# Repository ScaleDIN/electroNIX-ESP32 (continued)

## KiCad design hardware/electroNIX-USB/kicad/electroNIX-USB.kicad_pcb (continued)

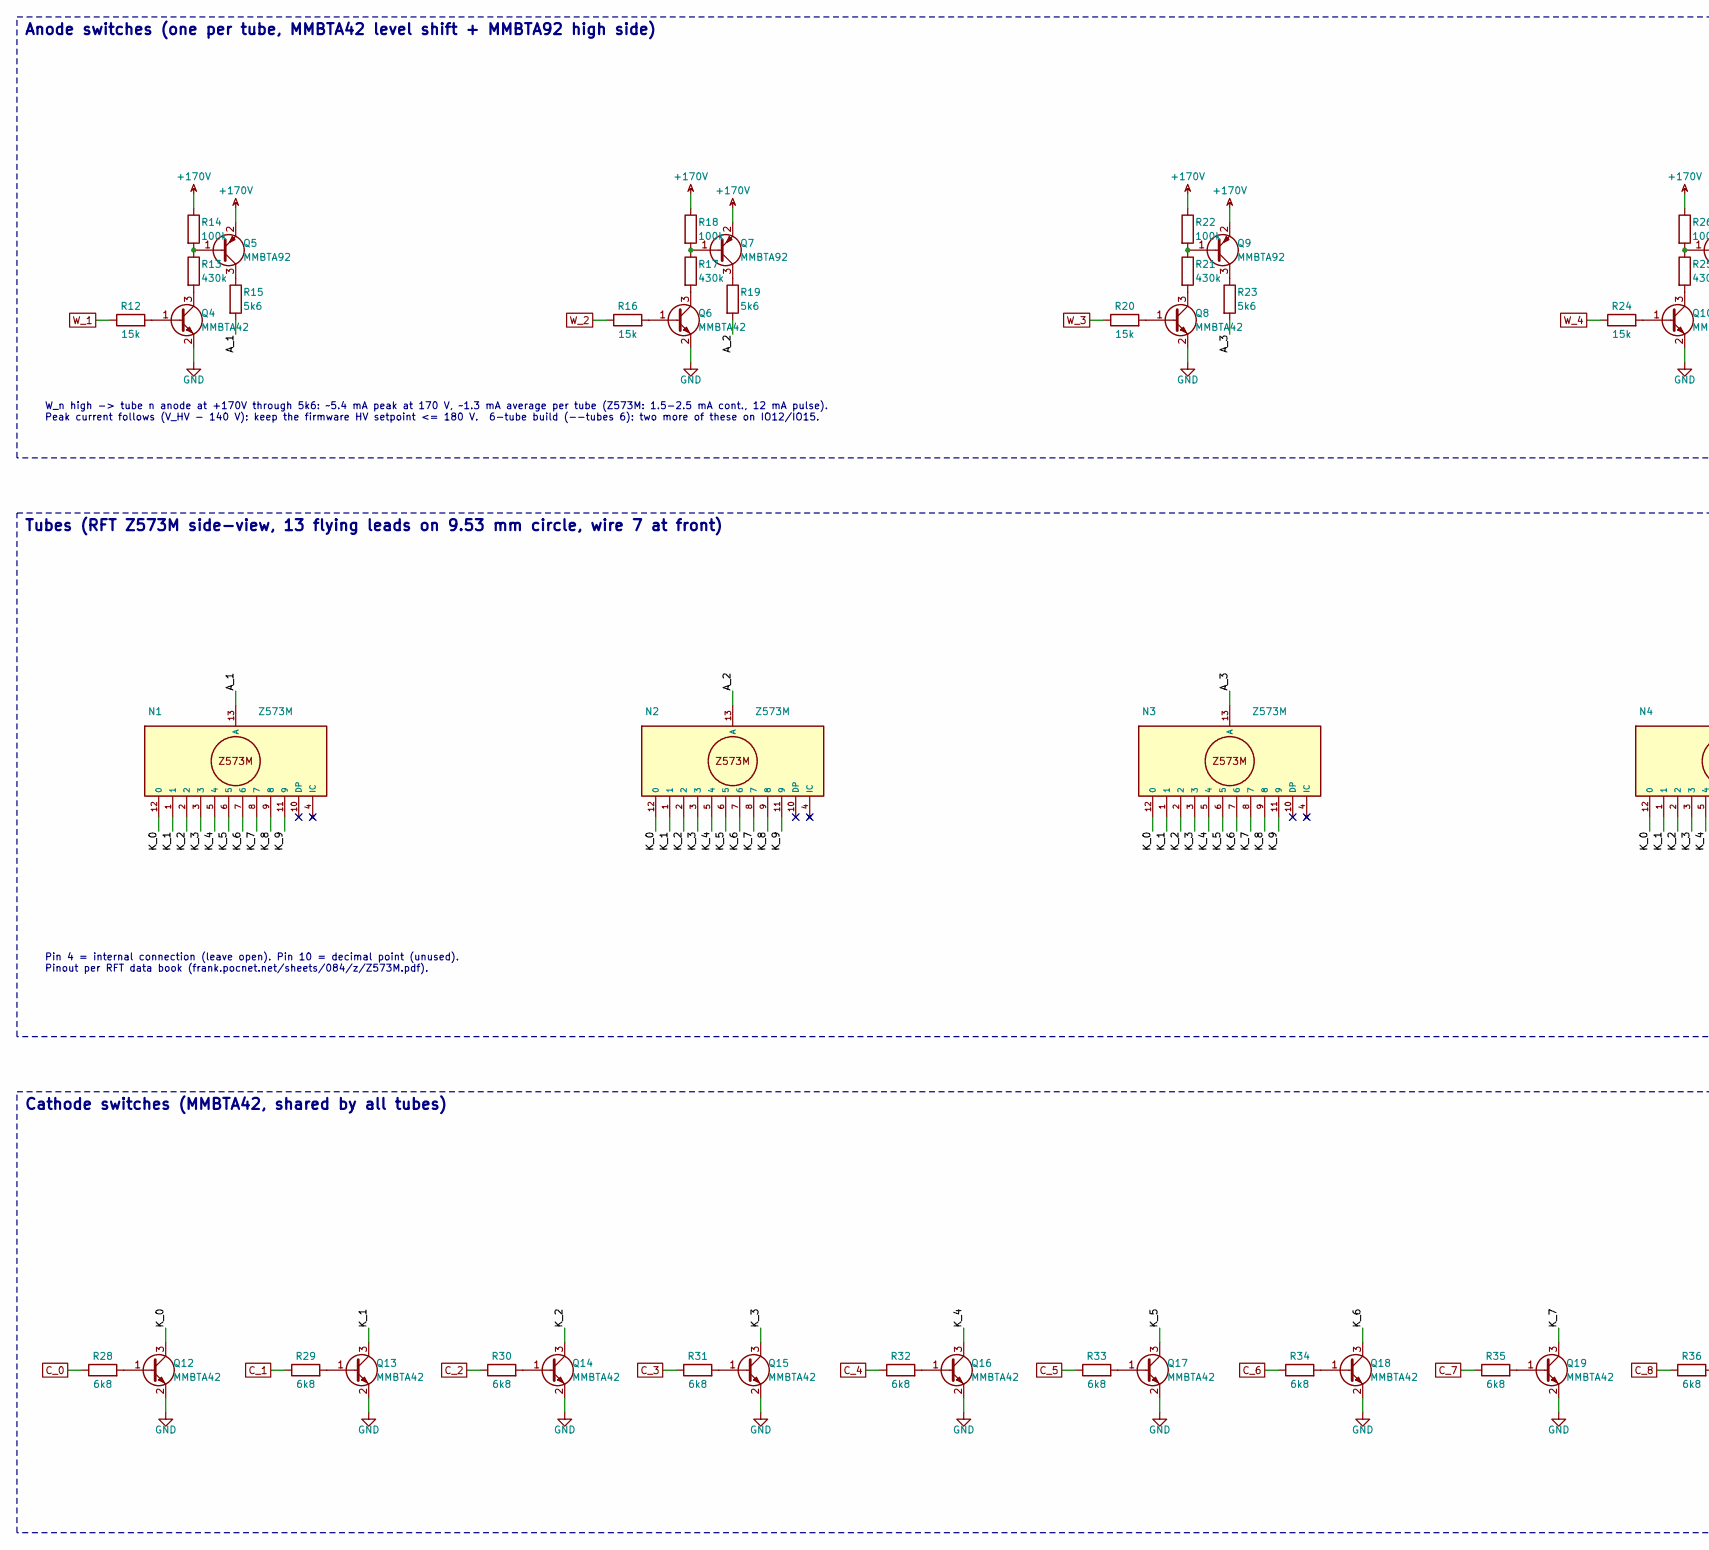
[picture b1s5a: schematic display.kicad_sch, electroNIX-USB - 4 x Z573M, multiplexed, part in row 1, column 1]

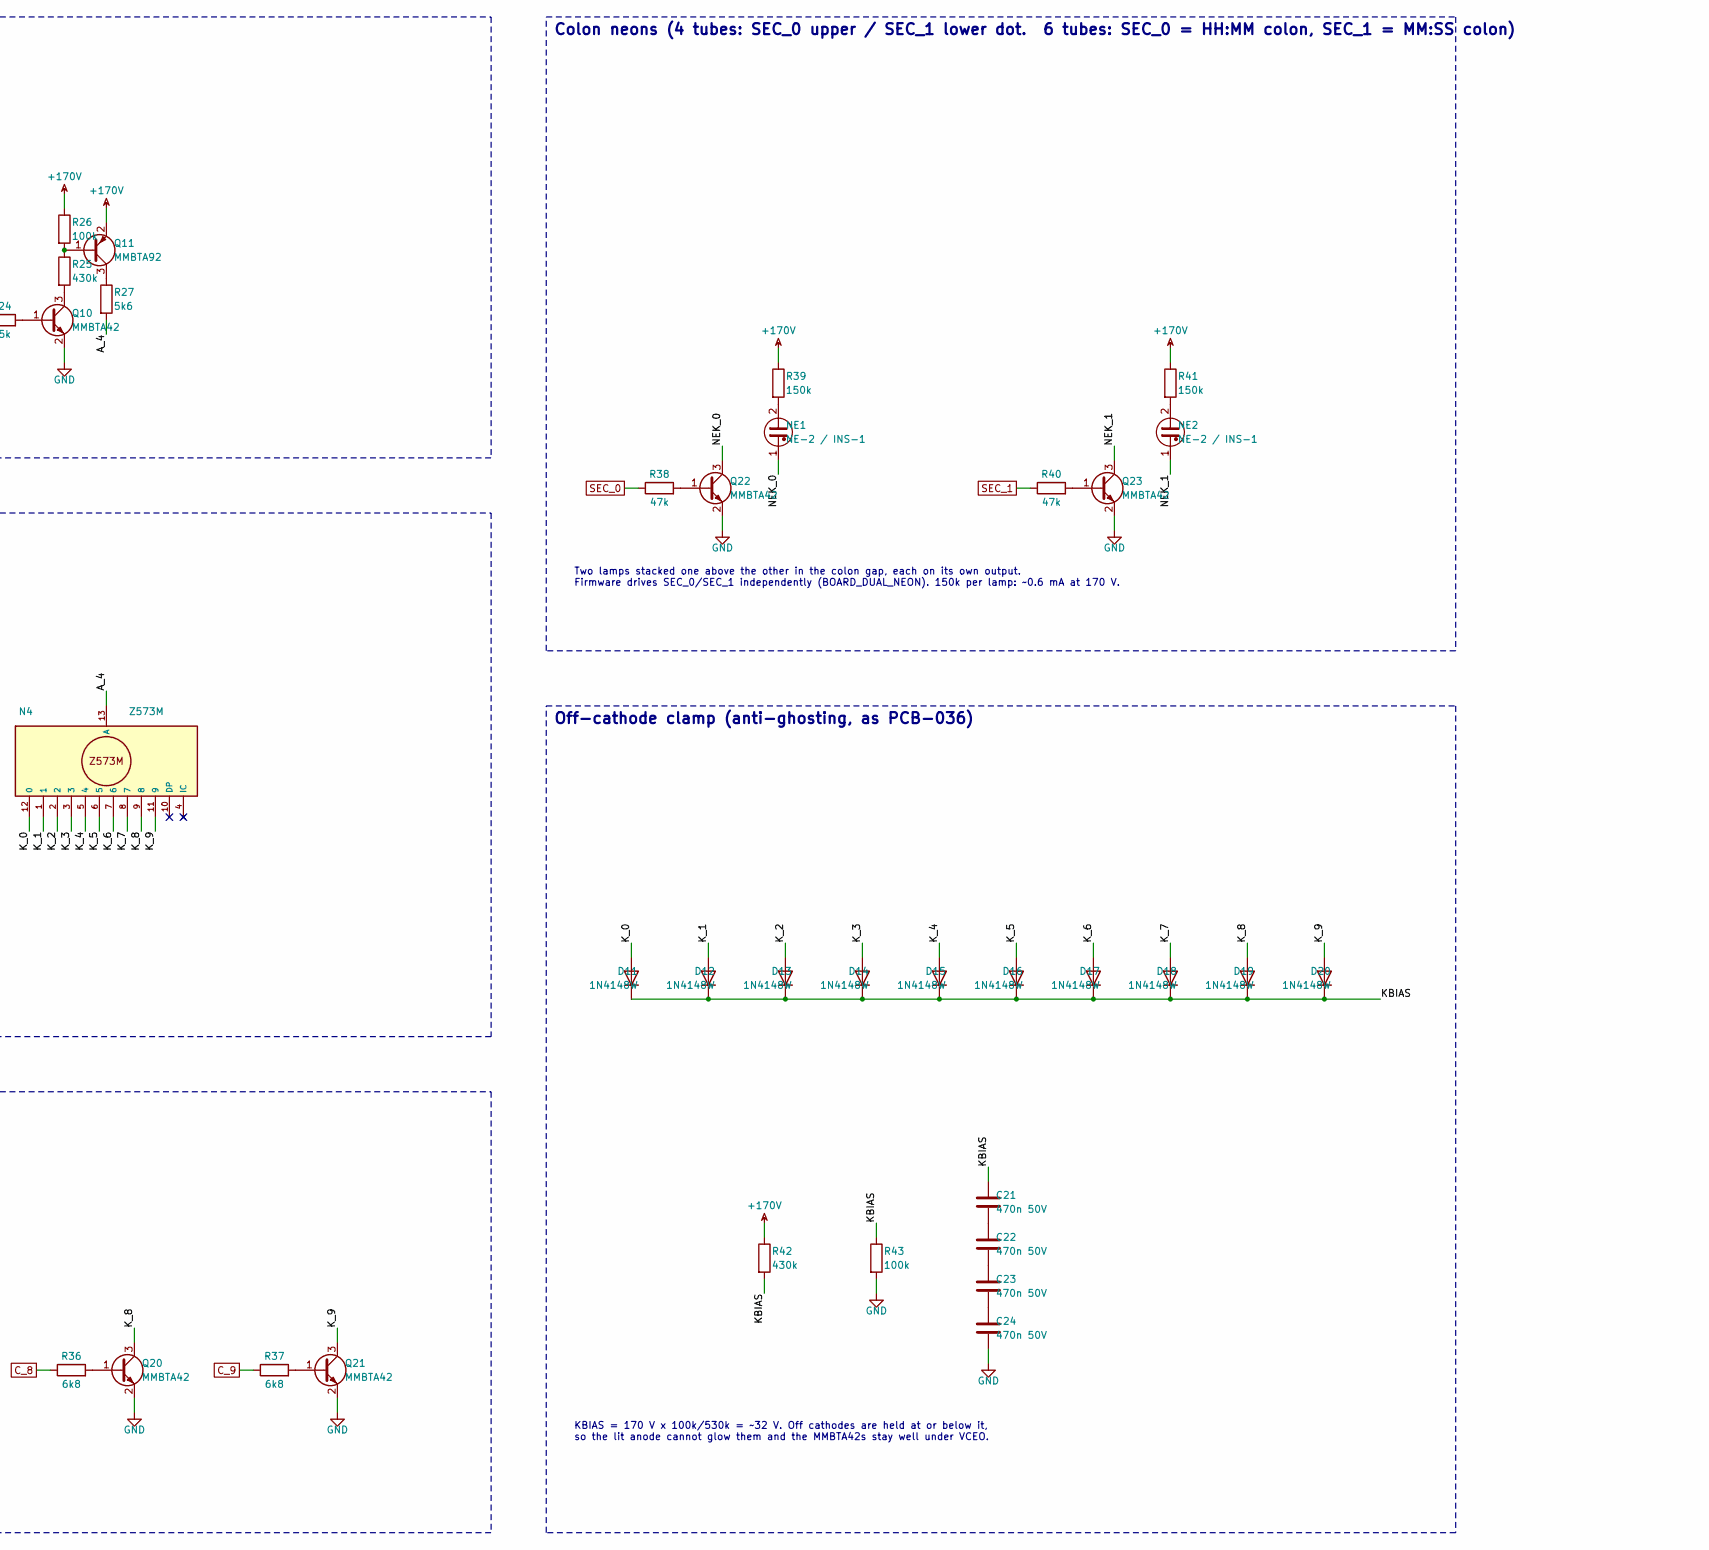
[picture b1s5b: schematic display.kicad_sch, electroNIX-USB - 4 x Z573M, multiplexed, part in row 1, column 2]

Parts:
C21, C22, C23, C24: 470n 50V; C_0805_2012Metric
D11, D12, D13, D14, D15, D16, D17, D18, D19, D20: 1N4148W; D_SOD-123
N1, N2, N3, N4: Z573M; Nixie_RFT_Z573M_Adapter
NE1, NE2: NE-2 / INS-1; Neon_P2.54mm
Q4, Q6, Q8, Q10, Q12, Q13, Q14, Q15, Q16, Q17, Q18, Q19, Q20, Q21, Q22, Q23: MMBTA42; SOT-23
Q5, Q7, Q9, Q11: MMBTA92; SOT-23
R12, R16, R20, R24: 15k; R_0805_2012Metric
R13, R17, R21, R25, R42: 430k; R_1206_3216Metric
R14, R18, R22, R26, R43: 100k; R_0805_2012Metric
R15, R19, R23, R27: 5k6; R_0805_2012Metric
R28, R29, R30, R31, R32, R33, R34, R35, R36, R37: 6k8; R_0805_2012Metric
R38, R40: 47k; R_0805_2012Metric
R39, R41: 150k; R_1206_3216Metric

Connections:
+170V: Q5.2 (E), Q7.2 (E), Q9.2 (E), Q11.2 (E), R14.1, R18.1, R22.1, R26.1, R39.1, R41.1, R42.1; also elsewhere on the board
/Display/A_1: N1.13 (A), R15.2
/Display/A_2: N2.13 (A), R19.2
/Display/A_3: N3.13 (A), R23.2
/Display/A_4: N4.13 (A), R27.2
/Display/KBIAS: C21.1, D11.1 (K), D12.1 (K), D13.1 (K), D14.1 (K), D15.1 (K), D16.1 (K), D17.1 (K), D18.1 (K), D19.1 (K), D20.1 (K), R42.2, R43.1
/Display/K_0: D11.2 (A), N1.12 (0), N2.12 (0), N3.12 (0), N4.12 (0), Q12.3 (C)
/Display/K_1: D12.2 (A), N1.1, N2.1, N3.1, N4.1, Q13.3 (C)
/Display/K_2: D13.2 (A), N1.2, N2.2, N3.2, N4.2, Q14.3 (C)
/Display/K_3: D14.2 (A), N1.3, N2.3, N3.3, N4.3, Q15.3 (C)
/Display/K_4: D15.2 (A), N1.5 (4), N2.5 (4), N3.5 (4), N4.5 (4), Q16.3 (C)
/Display/K_5: D16.2 (A), N1.6 (5), N2.6 (5), N3.6 (5), N4.6 (5), Q17.3 (C)
/Display/K_6: D17.2 (A), N1.7 (6), N2.7 (6), N3.7 (6), N4.7 (6), Q18.3 (C)
/Display/K_7: D18.2 (A), N1.8 (7), N2.8 (7), N3.8 (7), N4.8 (7), Q19.3 (C)
/Display/K_8: D19.2 (A), N1.9 (8), N2.9 (8), N3.9 (8), N4.9 (8), Q20.3 (C)
/Display/K_9: D20.2 (A), N1.11 (9), N2.11 (9), N3.11 (9), N4.11 (9), Q21.3 (C)
/Display/NEK_0: NE1.1, Q22.3 (C)
/Display/NEK_1: NE2.1, Q23.3 (C)
C_0: R28.1; also elsewhere on the board
C_1: R29.1; also elsewhere on the board
C_2: R30.1; also elsewhere on the board
C_3: R31.1; also elsewhere on the board
C_4: R32.1; also elsewhere on the board
C_5: R33.1; also elsewhere on the board
C_6: R34.1; also elsewhere on the board
C_7: R35.1; also elsewhere on the board
C_8: R36.1; also elsewhere on the board
C_9: R37.1; also elsewhere on the board
GND: C24.2, Q4.2 (E), Q6.2 (E), Q8.2 (E), Q10.2 (E), Q12.2 (E), Q13.2 (E), Q14.2 (E), Q15.2 (E), Q16.2 (E), Q17.2 (E), Q18.2 (E), Q19.2 (E), Q20.2 (E), Q21.2 (E), Q22.2 (E), Q23.2 (E), R43.2; also elsewhere on the board
unnamed: C21.2, C22.1
unnamed: C22.2, C23.1
unnamed: C23.2, C24.1
unnamed: NE1.2, R39.2
unnamed: NE2.2, R41.2
unnamed: Q4.1 (B), R12.2
unnamed: Q4.3 (C), R13.2
unnamed: Q5.1 (B), R13.1, R14.2
unnamed: Q5.3 (C), R15.1
unnamed: Q6.1 (B), R16.2
unnamed: Q6.3 (C), R17.2
unnamed: Q7.1 (B), R17.1, R18.2
unnamed: Q7.3 (C), R19.1
unnamed: Q8.1 (B), R20.2
unnamed: Q8.3 (C), R21.2
unnamed: Q9.1 (B), R21.1, R22.2
unnamed: Q9.3 (C), R23.1
unnamed: Q10.1 (B), R24.2
unnamed: Q10.3 (C), R25.2
unnamed: Q11.1 (B), R25.1, R26.2
unnamed: Q11.3 (C), R27.1
unnamed: Q12.1 (B), R28.2
unnamed: Q13.1 (B), R29.2
unnamed: Q14.1 (B), R30.2
unnamed: Q15.1 (B), R31.2
unnamed: Q16.1 (B), R32.2
unnamed: Q17.1 (B), R33.2
unnamed: Q18.1 (B), R34.2
unnamed: Q19.1 (B), R35.2
unnamed: Q20.1 (B), R36.2
unnamed: Q21.1 (B), R37.2
unnamed: Q22.1 (B), R38.2
unnamed: Q23.1 (B), R40.2
SEC_0: R38.1; also elsewhere on the board
SEC_1: R40.1; also elsewhere on the board
W_1: R12.1; also elsewhere on the board
W_2: R16.1; also elsewhere on the board
W_3: R20.1; also elsewhere on the board
W_4: R24.1; also elsewhere on the board

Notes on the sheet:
Anode switches (one per tube, MMBTA42 level shift + MMBTA92 high side)
W_n high -> tube n anode at +170V through 5k6: ~5.4 mA peak at 170 V, ~1.3 mA average per tube (Z573M: 1.5-2.5 mA cont., 12 mA pulse). Peak current follows (V_HV - 140 V): keep the firmware HV setpoint <= 180 V. 6-tube build (--tubes 6): two more of these on IO12/IO15.
Tubes (RFT Z573M side-view, 13 flying leads on 9.53 mm circle, wire 7 at front)
Pin 4 = internal connection (leave open). Pin 10 = decimal point (unused). Pinout per RFT data book (frank.pocnet.net/sheets/084/z/Z573M.pdf).
Cathode switches (MMBTA42, shared by all tubes)
Colon neons (4 tubes: SEC_0 upper / SEC_1 lower dot. 6 tubes: SEC_0 = HH:MM colon, SEC_1 = MM:SS colon)
Two lamps stacked one above the other in the colon gap, each on its own output. Firmware drives SEC_0/SEC_1 independently (BOARD_DUAL_NEON). 150k per lamp: ~0.6 mA at 170 V.
Off-cathode clamp (anti-ghosting, as PCB-036)
KBIAS = 170 V x 100k/530k = ~32 V. Off cathodes are held at or below it, so the lit anode cannot glow them and the MMBTA42s stay well under VCEO.

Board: 2 copper layers, 127 parts (116 on the bottom side), 94 nets, no tracks yet.

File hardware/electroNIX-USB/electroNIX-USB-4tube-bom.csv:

References,Qty,Value,Footprint
"C1, C10",2,22u 35V tant.,CP_EIA-7343-31_Kemet-D
C2,1,10u,C_1206_3216Metric
"C3, C6",2,22u,C_1206_3216Metric
"C4, C5, C7, C9, C11, C20",6,100n,C_0805_2012Metric
C8,1,1u,C_0805_2012Metric
"C12, C13, C14, C15, C16, C17, C18",7,2u2 100V,C_1210_3225Metric
C19,1,2u2 250V,CP_Radial_D8mm_P2.50mm_Lying
"C21, C22, C23, C24",4,470n 50V,C_0805_2012Metric
D1,1,SMBJ5.0CA,D_SMB
D2,1,BPW34 / HPDB3J,Osram_DIL2_4.3x4.65mm_P5.08mm
"D3, D4, D5, D6, D7, D8, D9",7,10MQ100N,D_SMA
D10,1,BAT54S,SOT-23
"D11, D12, D13, D14, D15, D16, D17, D18, D19, D20",10,1N4148W,D_SOD-123
F1,1,1.1 A hold,Fuse_1206_3216Metric
"H1, H2, H3, H4",4,M3,MountingHole_3.2mm_M3
J1,1,USB-C (USB 2.0),USB_C_Receptacle_GCT_USB4105-xx-A_16P_TopMnt_Horizontal
L1,1,33u WE 7447715330,L_Wuerth_WE-PD-Typ-LS
"N1, N2, N3, N4",4,Z573M,Nixie_RFT_Z573M_Adapter
"NE1, NE2",2,NE-2 / INS-1,Neon_P2.54mm
"Q1, Q2",2,MMBT3904,SOT-23
Q3,1,IRLR3110ZPBF,TO-252-2
"Q4, Q6, Q8, Q10, Q12, Q13, Q14, Q15, Q16, Q17, Q18, Q19, Q20, Q21, Q22, Q23",16,MMBTA42,SOT-23
"Q5, Q7, Q9, Q11",4,MMBTA92,SOT-23
"R1, R2",2,5k1,R_0805_2012Metric
"R3, R4, R5, R6, R9",5,10k,R_0805_2012Metric
R7,1,1M,R_0805_2012Metric
R8,1,10R,R_0805_2012Metric
"R10, R13, R17, R21, R25, R42",6,430k,R_1206_3216Metric
R11,1,6k2,R_0805_2012Metric
"R12, R16, R20, R24",4,15k,R_0805_2012Metric
"R14, R18, R22, R26, R43",5,100k,R_0805_2012Metric
"R15, R19, R23, R27",4,5k6,R_0805_2012Metric
"R28, R29, R30, R31, R32, R33, R34, R35, R36, R37",10,6k8,R_0805_2012Metric
"R38, R40",2,47k,R_0805_2012Metric
"R39, R41",2,150k,R_1206_3216Metric
U1,1,USBLC6-2SC6,SOT-23-6
U2,1,AMS1117-3.3,SOT-223-3_TabPin2
U3,1,CH340C,SOIC-16_3.9x9.9mm_P1.27mm
U4,1,ESP32-WROOM-32E-N4,ESP32-WROOM-32D

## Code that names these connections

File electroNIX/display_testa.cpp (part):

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  static const uint8_t ANODE_PINS[BOARD_TUBES] = {16, 17, 18, 19, 12, 15};
#endif
  static const uint8_t CATHODE_PINS[10] = {13, 14, 21, 22, 23, 25, 26, 27, 32, 33};
  static const uint8_t PIN_NEON0 = 4;   // SEC_0, unchanged from 4-tube boards
  static const uint8_t PIN_NEON1 = 5;   // SEC_1, unchanged from 4-tube boards
#else
  // Four-tube boards: electroNIX 4 and electroNIX 3.
  // fourTINY users should select BOARD_ELECTRONIX_4 — the pin maps are
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  static const uint8_t ANODE_PINS[BOARD_TUBES] = {16, 17, 18, 19};
  static const uint8_t CATHODE_PINS[10] = {13, 14, 21, 22, 23, 25, 26, 27, 32, 33};
  static const uint8_t PIN_NEON0 = 4;
  static const uint8_t PIN_NEON1 = 5;   // stock electroNIX 3 has no SEC_1 net --
                                          // this is where to land the bodge if
                                          // you add one (see WIRING.md). Driving
                                          // an unpopulated pin is harmless.
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// Former GPIO12 is now free on 4-tube boards; on 6-tube boards it carries
// anode W_5 (electroNIX 4+S) or SEC_1 colon neon (electroNIX 2).
static const uint8_t PIN_BUZZER   = 0;
static const uint8_t PIN_HV_SENSE = 35;    // KOMP_170V
static const uint8_t PIN_LIGHT    = 34;    // JASNOSC

// ---- HV regulation ---------------------------------------------------------
static const float    HV_DIV_RATIO = (430.0f + 6.2f) / 6.2f;   // 70.35 on all three
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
